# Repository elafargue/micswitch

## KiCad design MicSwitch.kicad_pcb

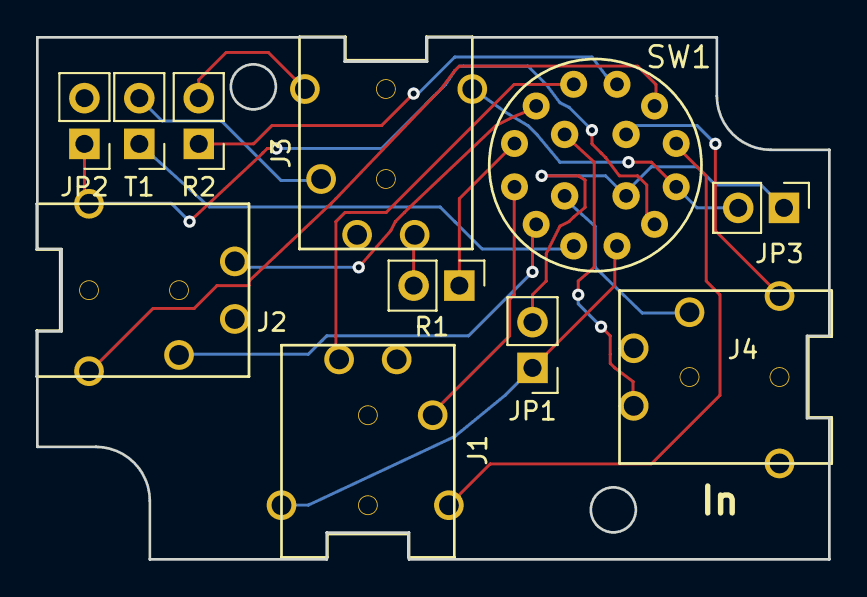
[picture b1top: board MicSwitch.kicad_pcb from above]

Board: 2 copper layers, 44.0 x 29.0 mm, 11 parts (0 on the bottom side), 19 nets.

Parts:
J1, J2, J3, J4: JACK_TRRS_4PINS; SJ-4351X
JP1, JP2, JP3: Jumper_NO_Small; Pin_Header_Straight_1x02_Pitch2.54mm
R1, R2: Jumper_NO_Small; Pin_Header_Straight_1x02_Pitch2.54mm
SW1: rotary4x3; Grayhill_Series56
T1: Jumper_NO_Small; Pin_Header_Straight_1x02_Pitch2.54mm

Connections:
GNDREF: J4.1, JP1.2, JP2.2, JP3.1, SW1.C1
unnamed: J1.1, JP1.1, SW1.3
unnamed: J1.2, SW1.6
unnamed: J1.3, SW1.9
unnamed: J1.4, SW1.12
unnamed: J2.1, JP2.1, SW1.2
unnamed: J2.2, SW1.5
unnamed: J2.3, SW1.8
unnamed: J2.4, SW1.11
unnamed: J3.1, JP3.2, SW1.1
unnamed: J3.2, T1.2
unnamed: J3.3, R1.2
unnamed: J3.4, R2.2
unnamed: J4.2, SW1.C2
unnamed: J4.3, SW1.C3
unnamed: J4.4, SW1.C4
unnamed: R1.1, SW1.7
unnamed: R2.1, SW1.10
unnamed: SW1.4, T1.1

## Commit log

2020-10-08 initial commit of base project files
2020-10-08 Add BoM documentation and 3D models
